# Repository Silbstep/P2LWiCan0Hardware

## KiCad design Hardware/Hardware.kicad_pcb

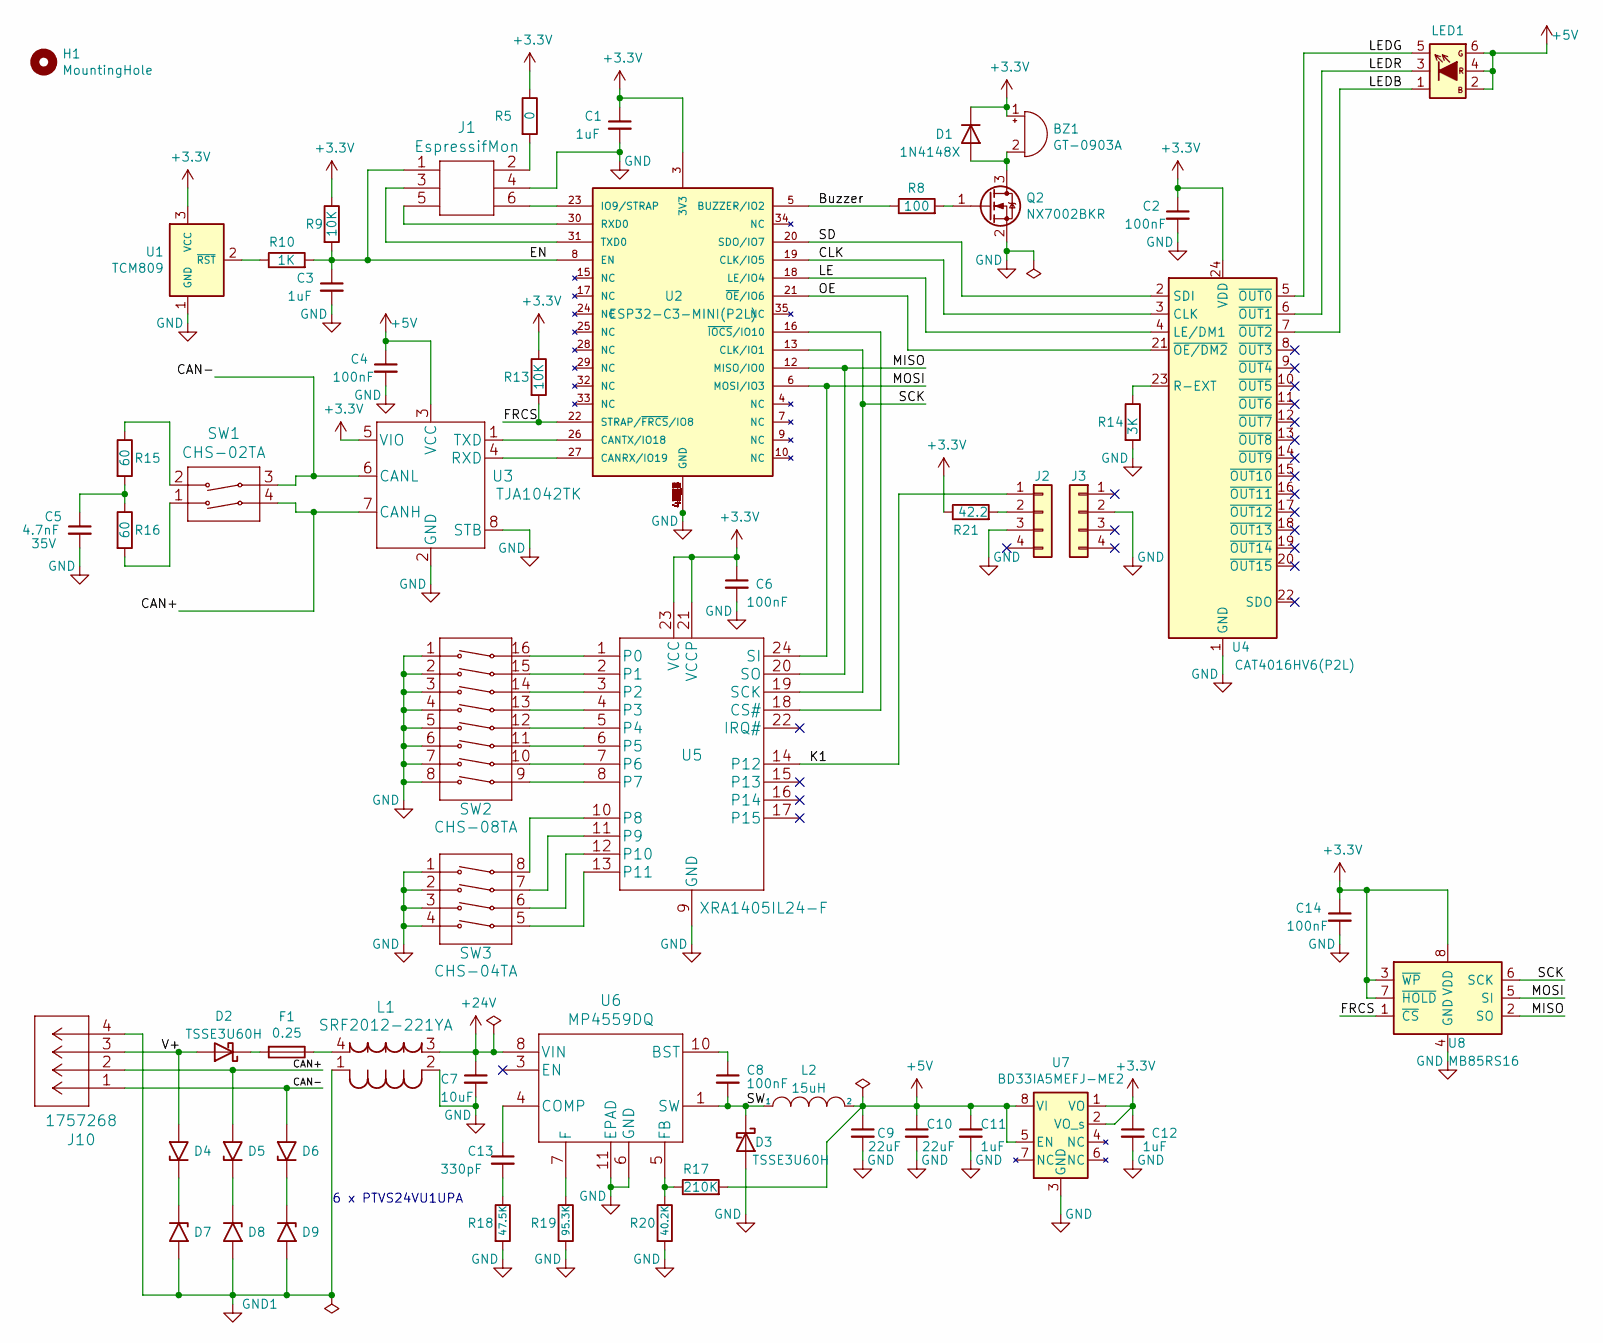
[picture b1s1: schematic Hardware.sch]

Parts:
BZ1: GT-0903A; MPN GT-0903A
C1, C3, C11, C12: 1uF; C_0603_1608Metric
C2, C4, C6, C8, C14: 100nF; C_0603_1608Metric
C5: 4.7nF; C_0603_1608Metric
C7: 10uF; C_1206_3216Metric; MPN CL31B106KBHNNNE
C9, C10: 22uF; C_1206_3216Metric
C13: 330pF; C_0603_1608Metric
D1: 1N4148X; D_SOD-523; MPN 1N4148X-TP
D2, D3: TSSE3U60H; TSSE3U45H; MPN TSSE3U60H
D4, D5, D6, D7, D8, D9: PTVS24VU1UPA; PTVS10VU1UPAZ; MPN PTVS24VU1UPAZ
F1: 0.25; Fuse_0603_1608Metric; MPN C2Q 250
H1: MountingHole; MountingHole_3mm_Pad
J1: EspressifMon; 3220-06-0100-00; MPN PR20B03VBDN
J2, J3: Conn_01x04(P2L); PinHeader_1x04_P2.54mm_Vertical_NoConn
J10: 1757268; OQ0454510000G; MPN OQ0454510000G
L1: SRF2012-221YA; MPN SRF2012-221YA
L2: 15uH; MPL-SE2512; MPN MPL-SE2512-150
LED1: LED150505; 150505M173300; MPN 150505M173300
Q2: NX7002BKR; SOT-23; MPN NX7002BKR
R5: 0; R_0603_1608Metric
R8: 100; R_0603_1608Metric
R9, R13: 10K; R_0603_1608Metric
R10: 1K; R_0603_1608Metric
R14: 3K; R_0603_1608Metric
R15, R16: 60; R_0805_2012Metric
R17: 210K; R_0603_1608Metric
R18: 47.5K; R_0603_1608Metric
R19: 95.3K; R_0603_1608Metric
R20: 40.2K; R_0603_1608Metric
R21: 42.2; R_0603_1608Metric
SW1: CHS-02TA; MPN 218-2LPSTJ
SW2: CHS-08TA; MPN 218-8LPSTJ
SW3: CHS-04TA; MPN 218-4LPSTJ
U1: TCM809; SOT-23; MPN APX809S05-29SA-7
U2: ESP32-C3-MINI(P2L); ESP32-C3-MINI-1-N4; MPN ESP32-C3-MINI-1-N4
U3: TJA1042TK; DFN-8-1EP_3x3mm_P0.65mm_EP1.6x2.40mm; MPN TJA1042T/3,118
U4: CAT4016HV6(P2L); CAT4016HV6-GT2; MPN CAT4016HV6-GT2
U5: XRA1405IL24-F; XRA1403IL24-F; MPN XRA1405IL24-F
U6: MP4559DQ; DFN-10-1EP_3x3mm_P0.5mm_EP1.7x2.5mm; MPN MP4559DQ-LF-Z
U7: BD33IA5MEFJ-ME2; MPN BD33IA5MEFJ-ME2
U8: MB85RS16; SOIC-8_3.9x4.9mm_P1.27mm; MPN MB85RS16NPNF-G-JNERE1

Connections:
+3V3: BZ1.1 (-), C1.1, C2.1, C6.1, C12.1, C14.1, D1.1 (K), R5.1, R9.1, R13.1, R21.1, U1.3 (VCC), U2.3 (3V3), U3.5 (VIO), U4.24 (VDD), U5.21 (VCCP), U5.23 (VCC), U7.1 (VO), U7.2 (VO_s), U8.3 (~WP), U8.7 (~HOLD), U8.8 (VDD)
+5V: C4.1, C9.1, C10.1, C11.1, L2.2, LED1.2 (AB), LED1.4 (AR), LED1.6 (AG), R17.2, U3.3 (VCC), U7.5 (EN), U7.8 (VI)
+24V: C7.1, L1.3, U6.8 (VIN), U6.9 (VIN)
/Buzzer: R8.1, U2.5 (BUZZER/IO2)
/CAN+: D5.1 (A1), D5.2 (A2), J10.2, SW1.4, U3.7 (CANH)
/CAN-: D6.1 (A1), D6.2 (A2), J10.1, SW1.3, U3.6 (CANL)
/CLK: U2.19 (CLK/IO5), U4.3 (CLK)
/EN: C3.1, J1.1, R9.2, R10.2, U2.8 (EN)
/FRCS: R13.2, U2.22 (STRAP/~FRCS~/IO8), U8.1 (~CS)
/K1: J2.1, U5.14 (P12)
/LE: U2.18 (LE/IO4), U4.4 (LE/DM1)
/LEDB: LED1.1 (KB), U4.7 (~OUT2)
/LEDG: LED1.5 (KG), U4.5 (~OUT0)
/LEDR: LED1.3 (KR), U4.6 (~OUT1)
/MISO: U2.12 (MISO/IO0), U5.20 (SO), U8.2 (SO)
/MOSI: U2.6 (MOSI/IO3), U5.24 (SI), U8.5 (SI)
/OE: U2.21 (~OE~/IO6), U4.21 (~OE/DM2)
/SCK: U2.13 (CLK/IO1), U5.19 (SCK), U8.6 (SCK)
/SD: U2.20 (SDO/IO7), U4.2 (SDI)
/V+: D2.A, D4.1 (A1), D4.2 (A2), J10.3
EP: C1.2, C2.2, C3.2, C4.2, C5.2, C6.2, C7.2, C9.2, C10.2, C11.2, C12.2, C14.2, D3.A, J1.4, J2.3, J3.2, L1.2, Q2.2 (S), R14.2, R18.2, R19.2, R20.2, SW2.1, SW2.2, SW2.3, SW2.4, SW2.5, SW2.6, SW2.7, SW2.8, SW3.1, SW3.2, SW3.3, SW3.4, U1.1 (GND), U2.1 (GND), U2.2 (GND), U2.11 (GND), U2.14 (GND), U2.36 (GND), U2.37 (GND), U2.38 (GND), U2.39 (GND), U2.40 (GND), U2.41 (GND), U2.42 (GND), U2.43 (GND), U2.44 (GND), U2.45 (GND), U2.46 (GND), U2.47 (GND), U2.48 (GND), U2.49_1 (GND), U2.49_2 (GND), U2.49_3 (GND), U2.49_4 (GND), U2.49_5 (GND), U2.49_6 (GND), U2.49_7 (GND), U2.49_8 (GND), U2.49_9 (GND), U2.50 (GND), U2.51 (GND), U2.52 (GND), U2.53 (GND), U3.2 (GND), U3.8 (STB), U4.1 (GND), U4.25 (EP), U5.9 (GND), U5.25 (GND), U6.6 (GND), U6.11 (EPAD), U7.3 (GND), U7.9 (GND), U8.4 (GND)
GND1: D7.1 (A1), D7.2 (A2), D8.1 (A1), D8.2 (A2), D9.1 (A1), D9.2 (A2), J10.4, L1.1
unnamed: BZ1.2 (+), D1.2 (A), Q2.3 (D)
unnamed: C5.1, R15.2, R16.1
unnamed: C8.1, U6.10 (BST)
unnamed: C13.1, U6.4 (COMP)
unnamed: C13.2, R18.1
unnamed: D2.C (K), F1.2
unnamed: D4.3 (K1), D4.4 (K2), D7.3 (K1), D7.4 (K2)
unnamed: D5.3 (K1), D5.4 (K2), D8.3 (K1), D8.4 (K2)
unnamed: D6.3 (K1), D6.4 (K2), D9.3 (K1), D9.4 (K2)
unnamed: F1.1, L1.4
unnamed: J1.2, R5.2
unnamed: J1.3, U2.31 (TXD0)
unnamed: J1.5, U2.30 (RXD0)
unnamed: J1.6, U2.23 (IO9/STRAP)
unnamed: J2.2, R21.2
unnamed: Q2.1 (G), R8.2
unnamed: R10.1, U1.2 (~RST~)
unnamed: R14.1, U4.23 (R-EXT)
unnamed: R15.1, SW1.2
unnamed: R16.2, SW1.1
unnamed: R17.1, R20.1, U6.5 (FB)
unnamed: R19.1, U6.7 (F)
unnamed: SW2.9, U5.8 (P7)
unnamed: SW2.10, U5.7 (P6)
unnamed: SW2.11, U5.6 (P5)
unnamed: SW2.12, U5.5 (P4)
unnamed: SW2.13, U5.4 (P3)
unnamed: SW2.14, U5.3 (P2)
unnamed: SW2.15, U5.2 (P1)
unnamed: SW2.16, U5.1 (P0)
unnamed: SW3.5, U5.13 (P11)
unnamed: SW3.6, U5.12 (P10)
unnamed: SW3.7, U5.11 (P9)
unnamed: SW3.8, U5.10 (P8)
unnamed: U2.16 (~IOCS~/IO10), U5.18 (CS#)
unnamed: U2.26 (CANTX/IO18), U3.1 (TXD)
unnamed: U2.27 (CANRX/IO19), U3.4 (RXD)
SW: C8.2, D3.C (K), L2.1, U6.1 (SW), U6.2 (SW)

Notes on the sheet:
6 x PTVS24VU1UPA

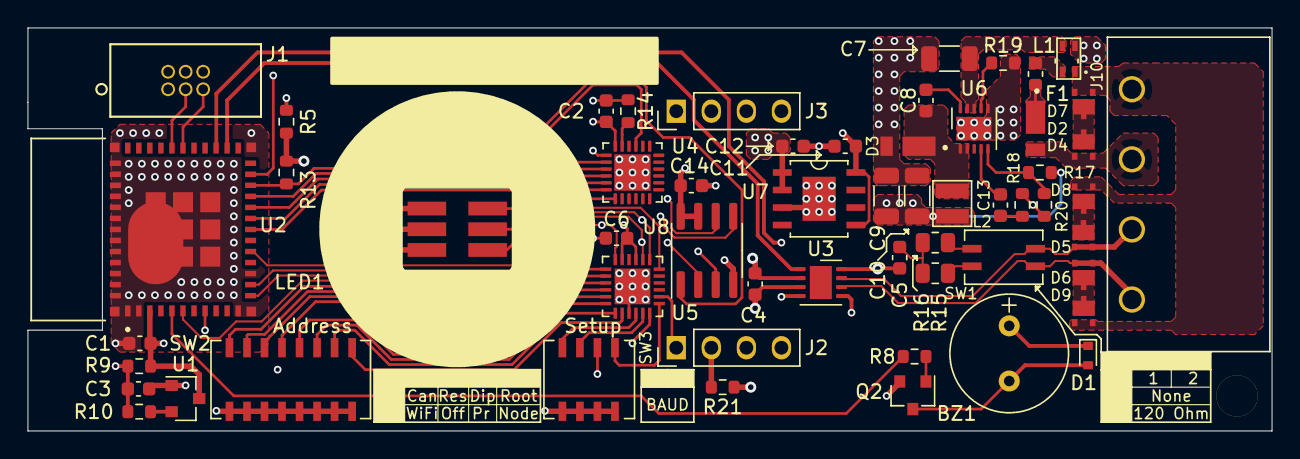
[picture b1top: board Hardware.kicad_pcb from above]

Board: 4 copper layers, 90.2 x 29.2 mm, 58 parts (0 on the bottom side), 60 nets.

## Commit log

2023-03-03 Hardware design for P2LWiCan0. Production version 1

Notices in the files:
parts and their libraries:
Copyright 2016 Accelerated Designs. All rights reserved.
